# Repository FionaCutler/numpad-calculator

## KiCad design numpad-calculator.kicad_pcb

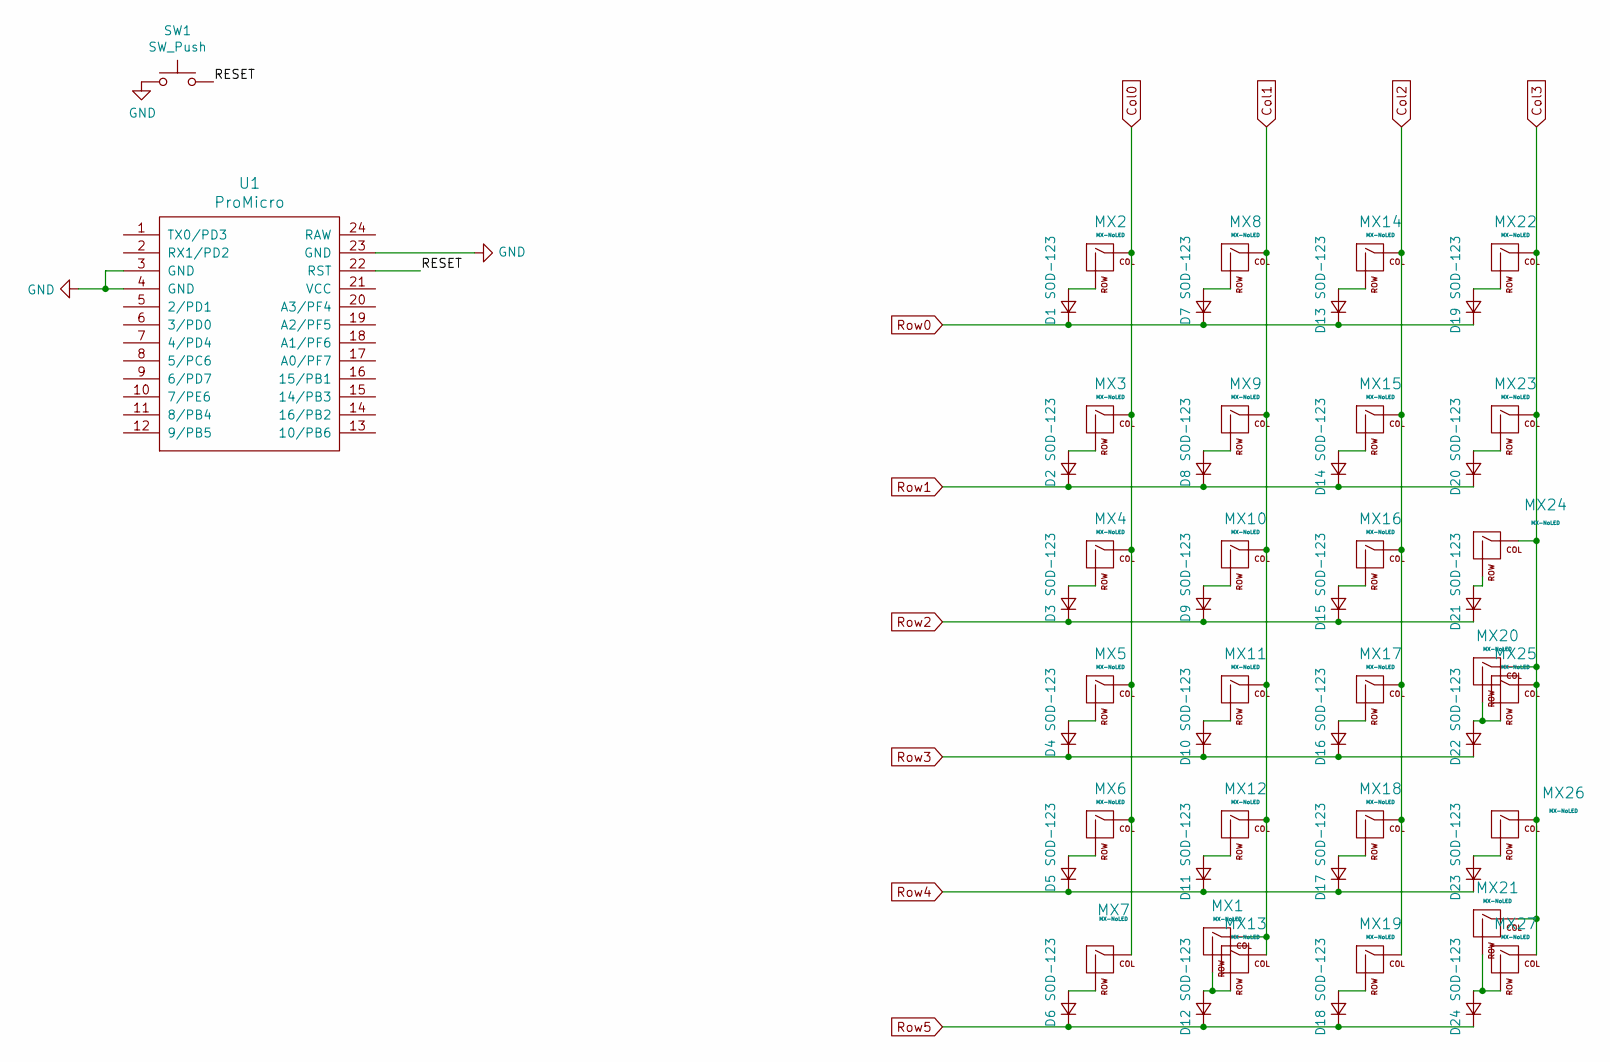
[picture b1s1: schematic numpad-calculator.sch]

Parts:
D1, D2, D3, D4, D5, D6, D7, D8, D9, D10, D11, D12, D13, D14, D15, D16, D17, D18, D19, D20, D21, D22, D23, D24: SOD-123; Diode
MX1: MX-NoLED; Hybrid_PCB_200H
MX2, MX3, MX4, MX5, MX6, MX7, MX8, MX9, MX10, MX11, MX12, MX13, MX14, MX15, MX16, MX17, MX18, MX19, MX22, MX23, MX24, MX25, MX26, MX27: MX-NoLED; Hybrid_PCB_100H
MX20, MX21: MX-NoLED; Hybrid_PCB_200V
SW1: SW_Push; SW_PUSH_6mm
U1: ProMicro; ArduinoProMicro-Mini-USB-ZigZag

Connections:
/RESET: SW1.2, U1.22 (RST)
Col0: MX2.1 (COL), MX3.1 (COL), MX4.1 (COL), MX5.1 (COL), MX6.1 (COL), MX7.1 (COL)
Col1: MX1.1 (COL), MX8.1 (COL), MX9.1 (COL), MX10.1 (COL), MX11.1 (COL), MX12.1 (COL), MX13.1 (COL)
Col2: MX14.1 (COL), MX15.1 (COL), MX16.1 (COL), MX17.1 (COL), MX18.1 (COL), MX19.1 (COL)
Col3: MX20.1 (COL), MX21.1 (COL), MX22.1 (COL), MX23.1 (COL), MX24.1 (COL), MX25.1 (COL), MX26.1 (COL), MX27.1 (COL)
GND: SW1.1, U1.3 (GND), U1.4 (GND), U1.23 (GND)
unnamed: D1.2 (A), MX2.2 (ROW)
unnamed: D2.2 (A), MX3.2 (ROW)
unnamed: D3.2 (A), MX4.2 (ROW)
unnamed: D4.2 (A), MX5.2 (ROW)
unnamed: D5.2 (A), MX6.2 (ROW)
unnamed: D6.2 (A), MX7.2 (ROW)
unnamed: D7.2 (A), MX8.2 (ROW)
unnamed: D8.2 (A), MX9.2 (ROW)
unnamed: D9.2 (A), MX10.2 (ROW)
unnamed: D10.2 (A), MX11.2 (ROW)
unnamed: D11.2 (A), MX12.2 (ROW)
unnamed: D12.2 (A), MX1.2 (ROW), MX13.2 (ROW)
unnamed: D13.2 (A), MX14.2 (ROW)
unnamed: D14.2 (A), MX15.2 (ROW)
unnamed: D15.2 (A), MX16.2 (ROW)
unnamed: D16.2 (A), MX17.2 (ROW)
unnamed: D17.2 (A), MX18.2 (ROW)
unnamed: D18.2 (A), MX19.2 (ROW)
unnamed: D19.2 (A), MX22.2 (ROW)
unnamed: D20.2 (A), MX23.2 (ROW)
unnamed: D21.2 (A), MX24.2 (ROW)
unnamed: D22.2 (A), MX20.2 (ROW), MX25.2 (ROW)
unnamed: D23.2 (A), MX26.2 (ROW)
unnamed: D24.2 (A), MX21.2 (ROW), MX27.2 (ROW)
Row0: D1.1 (K), D7.1 (K), D13.1 (K), D19.1 (K)
Row1: D2.1 (K), D8.1 (K), D14.1 (K), D20.1 (K)
Row2: D3.1 (K), D9.1 (K), D15.1 (K), D21.1 (K)
Row3: D4.1 (K), D10.1 (K), D16.1 (K), D22.1 (K)
Row4: D5.1 (K), D11.1 (K), D17.1 (K), D23.1 (K)
Row5: D6.1 (K), D12.1 (K), D18.1 (K), D24.1 (K)

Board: 2 copper layers, 53 parts (25 on the bottom side), 36 nets, no tracks yet.

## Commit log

2019-11-22 Initialized project
2019-11-22 Added Keebio parts
2019-11-22 Added Keebio components
2019-11-22 Create matrix
2019-11-22 Create footprints
2019-11-22 Basic layout
